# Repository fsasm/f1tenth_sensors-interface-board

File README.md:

# f1tenth_sensors-interface-board
Extension board for F1tenth cars with sensors and interfaces for humans (LEDs, display, buttons, etc.)

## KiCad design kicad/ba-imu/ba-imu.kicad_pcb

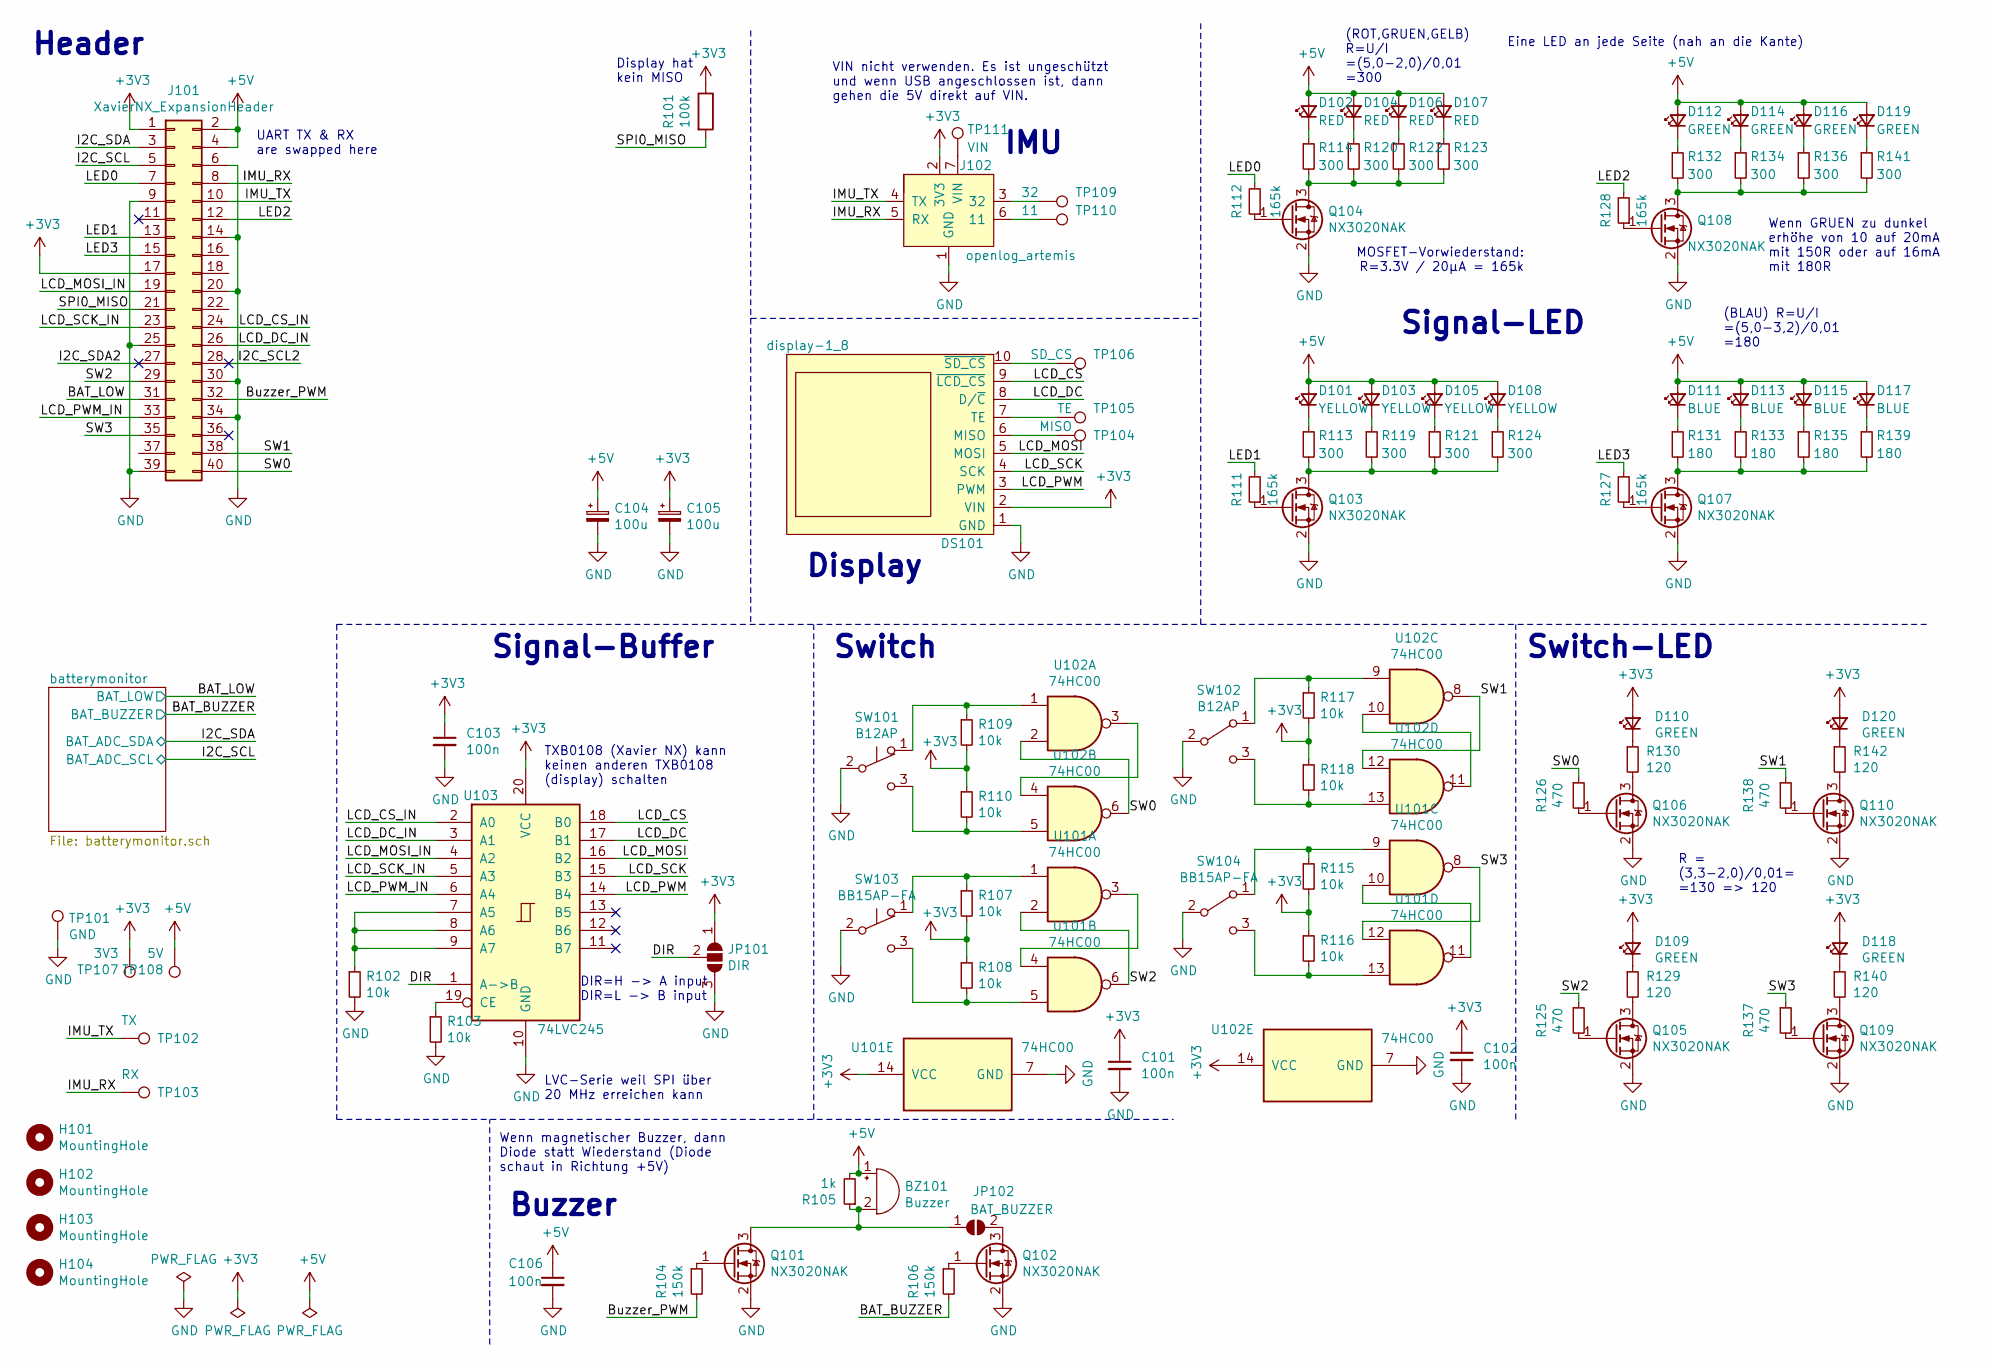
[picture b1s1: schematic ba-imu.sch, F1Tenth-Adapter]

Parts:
BZ101: Buzzer; Buzzer_TDK_PS1240P02BT_D12.2mm_H6.5mm; MPN PS1240P02BT; Digi-Key PN 445-2525-1-ND
C101, C102, C103, C106: 100n; C_1206_3216Metric
C104, C105: 100u; CP_Elec_6.3x7.7
D101, D103, D105, D108: YELLOW; LED_1206_3216Metric; MPN 156120YS75000; Digi-Key PN 732-5034-1-ND
D102, D104, D106, D107: RED; LED_1206_3216Metric; MPN 156120RS75000; Digi-Key PN 732-5030-1-ND
D109, D110, D112, D114, D116, D118, D119, D120: GREEN; LED_1206_3216Metric; MPN HSMQ-C150; Digi-Key PN 516-1444-1-ND
D111, D113, D115, D117: BLUE; LED_1206_3216Metric; MPN 156125BS75000; Digi-Key PN 732-13392-1-ND
DS101: display-1_8; display_SIP-10
H101, H102, H103, H104: MountingHole; MountingHole_2.5mm
J101: XavierNX_ExpansionHeader; PinHeader_2x20_P2.54mm_Vertical
J102: openlog_artemis; imu_SIP-7
JP101: DIR; SolderJumper-3_P1.3mm_Open_RoundedPad1.0x1.5mm
JP102: BAT_BUZZER; SolderJumper-2_P1.3mm_Open_RoundedPad1.0x1.5mm
Q101, Q102, Q103, Q104, Q105, Q106, Q107, Q108, Q109, Q110: NX3020NAK; SOT-23; MPN NX3020NAK; Digi-Key PN 1727-1285-1-ND
R101: 100k; R_1206_3216Metric
R102, R103, R107, R108, R109, R110, R115, R116, R117, R118: 10k; R_1206_3216Metric
R104, R106: 150k; R_1206_3216Metric
R105: 1k; R_1206_3216Metric
R111, R112, R127, R128: 165k; R_1206_3216Metric
R113, R114, R119, R120, R121, R122, R123, R124, R132, R134, R136, R141: 300; R_1206_3216Metric
R125, R126, R137, R138: 470; R_1206_3216Metric
R129, R130, R140, R142: 120; R_1206_3216Metric
R131, R133, R135, R139: 180; R_1206_3216Metric
SW101: B12AP; SW_Nidec_CFP2-1FC-AW; MPN B12AP; Digi-Key PN 360-1012-ND
SW102: B12AP; SW_Nidec_CF-LD-1DC-AR2W; MPN B12AP; Digi-Key PN 360-1012-ND
SW103: BB15AP-FA; SW_Nidec_CFP2-1FC-AW; MPN BB15AP-FA; Digi-Key PN 360-3753-ND
SW104: BB15AP-FA; SW_Nidec_CF-LD-1DC-AR2W; MPN BB15AP-FA; Digi-Key PN 360-3753-ND
TP101: GND; TestPoint_Pad_1.5x1.5mm
TP102: TX; TestPoint_Pad_D1.5mm
TP103: RX; TestPoint_Pad_D1.5mm
TP104: MISO; TestPoint_Pad_D1.5mm
TP105: TE; TestPoint_Pad_D1.5mm
TP106: SD_CS; TestPoint_Pad_D1.5mm
TP107: 3V3; TestPoint_Pad_D1.5mm
TP108: 5V; TestPoint_Pad_D1.5mm
TP109: 32; TestPoint_Pad_D1.5mm
TP110: 11; TestPoint_Pad_D1.5mm
TP111: VIN; TestPoint_Pad_D1.5mm
U101, U102: 74HC00; SOIC-14_3.9x8.7mm_P1.27mm; MPN SN74HC00DE4; Digi-Key PN 296-52930-ND
U103: 74LVC245; SOIC-20W_7.5x12.8mm_P1.27mm; MPN SN74LVC245ADW; Digi-Key PN 296-1232-5-ND

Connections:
+3V3: C101.1, C102.1, C103.1, C105.1, D109.2 (A), D110.2 (A), D118.2 (A), D120.2 (A), DS101.2 (VIN), J101.1, J101.17, J102.2 (3V3), JP101.1 (A), R101.1, R107.2, R108.1, R109.2, R110.1, R115.2, R116.1, R117.2, R118.1, TP107.1, U101.14 (VCC), U102.14 (VCC), U103.20 (VCC); also elsewhere on the board
+5V: BZ101.1 (-), C104.1, C106.1, D101.2 (A), D102.2 (A), D103.2 (A), D104.2 (A), D105.2 (A), D106.2 (A), D107.2 (A), D108.2 (A), D111.2 (A), D112.2 (A), D113.2 (A), D114.2 (A), D115.2 (A), D116.2 (A), D117.2 (A), D119.2 (A), J101.2, J101.4, R105.2, TP108.1
/BAT_BUZZER: R106.2; also elsewhere on the board
/BAT_LOW: J101.31; also elsewhere on the board
/Buzzer_PWM: J101.32, R104.2
/DIR: JP101.2 (C), U103.1 (A->B)
/I2C_SCL: J101.5; also elsewhere on the board
/I2C_SCL2: J101.28
/I2C_SDA: J101.3; also elsewhere on the board
/I2C_SDA2: J101.27
/IMU_RX: J101.8, J102.5 (RX), TP103.1
/IMU_TX: J101.10, J102.4 (TX), TP102.1
/LCD_CS: DS101.9 (~LCD_CS), U103.18 (B0)
/LCD_CS_IN: J101.24, U103.2 (A0)
/LCD_DC: DS101.8 (D/~C), U103.17 (B1)
/LCD_DC_IN: J101.26, U103.3 (A1)
/LCD_MOSI: DS101.5 (MOSI), U103.16 (B2)
/LCD_MOSI_IN: J101.19, U103.4 (A2)
/LCD_PWM: DS101.3 (PWM), U103.14 (B4)
/LCD_PWM_IN: J101.33, U103.6 (A4)
/LCD_SCK: DS101.4 (SCK), U103.15 (B3)
/LCD_SCK_IN: J101.23, U103.5 (A3)
/LED0: J101.7, R112.2
/LED1: J101.13, R111.2
/LED2: J101.12, R128.2
/LED3: J101.15, R127.2
/SPI0_MISO: J101.21, R101.2
/SW0: J101.40, R126.1, U102.2, U102.6
/SW1: J101.38, R138.1, U102.8, U102.12
/SW2: J101.29, R125.1, U101.2, U101.6
/SW3: J101.35, R137.1, U101.8, U101.12
GND: C101.2, C102.2, C103.2, C104.2, C105.2, C106.2, DS101.1 (GND), J101.6, J101.9, J101.14, J101.20, J101.25, J101.30, J101.34, J101.39, J102.1 (GND), JP101.3 (B), Q101.2 (S), Q102.2 (S), Q103.2 (S), Q104.2 (S), Q105.2 (S), Q106.2 (S), Q107.2 (S), Q108.2 (S), Q109.2 (S), Q110.2 (S), R102.2, R103.2, SW101.2 (B), SW102.2 (B), SW103.2 (B), SW104.2 (B), TP101.1, U101.7 (GND), U102.7 (GND), U103.10 (GND); also elsewhere on the board
unnamed: BZ101.2 (+), JP102.1 (A), Q101.3 (D), R105.1
unnamed: D101.1 (K), R113.1
unnamed: D102.1 (K), R114.1
unnamed: D103.1 (K), R119.1
unnamed: D104.1 (K), R120.1
unnamed: D105.1 (K), R121.1
unnamed: D106.1 (K), R122.1
unnamed: D107.1 (K), R123.1
unnamed: D108.1 (K), R124.1
unnamed: D109.1 (K), R129.1
unnamed: D110.1 (K), R130.1
unnamed: D111.1 (K), R131.1
unnamed: D112.1 (K), R132.1
unnamed: D113.1 (K), R133.1
unnamed: D114.1 (K), R134.1
unnamed: D115.1 (K), R135.1
unnamed: D116.1 (K), R136.1
unnamed: D117.1 (K), R139.1
unnamed: D118.1 (K), R140.1
unnamed: D119.1 (K), R141.1
unnamed: D120.1 (K), R142.1
unnamed: DS101.6 (MISO), TP104.1
unnamed: DS101.7 (TE), TP105.1
unnamed: DS101.10 (~SD_CS), TP106.1
unnamed: J102.3 (32), TP109.1
unnamed: J102.6 (11), TP110.1
unnamed: J102.7 (VIN), TP111.1
unnamed: JP102.2 (B), Q102.3 (D)
unnamed: Q101.1 (G), R104.1
unnamed: Q102.1 (G), R106.1
unnamed: Q103.1 (G), R111.1
unnamed: Q103.3 (D), R113.2, R119.2, R121.2, R124.2
unnamed: Q104.1 (G), R112.1
unnamed: Q104.3 (D), R114.2, R120.2, R122.2, R123.2
unnamed: Q105.1 (G), R125.2
unnamed: Q105.3 (D), R129.2
unnamed: Q106.1 (G), R126.2
unnamed: Q106.3 (D), R130.2
unnamed: Q107.1 (G), R127.1
unnamed: Q107.3 (D), R131.2, R133.2, R135.2, R139.2
unnamed: Q108.1 (G), R128.1
unnamed: Q108.3 (D), R132.2, R134.2, R136.2, R141.2
unnamed: Q109.1 (G), R137.2
unnamed: Q109.3 (D), R140.2
unnamed: Q110.1 (G), R138.2
unnamed: Q110.3 (D), R142.2
unnamed: R102.1, U103.7 (A5), U103.8 (A6), U103.9 (A7)
unnamed: R103.1, U103.19 (CE)
unnamed: R107.1, SW103.1 (A), U101.1
unnamed: R108.2, SW103.3 (C), U101.5
unnamed: R109.1, SW101.1 (A), U102.1
unnamed: R110.2, SW101.3 (C), U102.5
unnamed: R115.1, SW104.1 (A), U101.9
unnamed: R116.2, SW104.3 (C), U101.13
unnamed: R117.1, SW102.1 (A), U102.9
unnamed: R118.2, SW102.3 (C), U102.13
unnamed: U101.3, U101.4
unnamed: U101.10, U101.11
unnamed: U102.3, U102.4
unnamed: U102.10, U102.11

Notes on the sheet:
(ROT,GRUEN,GELB) R=U/I =(5,0-2,0)/0,01 =300
Wenn magnetischer Buzzer, dann Diode statt Wiederstand (Diode schaut in Richtung +5V)
VIN nicht verwenden. Es ist ungeschützt und wenn USB angeschlossen ist, dann gehen die 5V direkt auf VIN.
Eine LED an jede Seite (nah an die Kante)
DIR=H -> A input DIR=L -> B input
TXB0108 (Xavier NX) kann keinen anderen TXB0108 (display) schalten
(BLAU) R=U/I =(5,0-3,2)/0,01 =180
UART TX & RX are swapped here
Switch-LED
Switch
Buzzer
Signal-LED
LVC-Serie weil SPI über 20 MHz erreichen kann
Signal-Buffer
IMU
Display
Header
Display hat kein MISO
R = (3,3-2,0)/0,01= =130 => 120
Wenn GRUEN zu dunkel erhöhe von 10 auf 20mA mit 150R oder auf 16mA mit 180R
MOSFET-Vorwiederstand: R=3.3V / 20µA = 165k

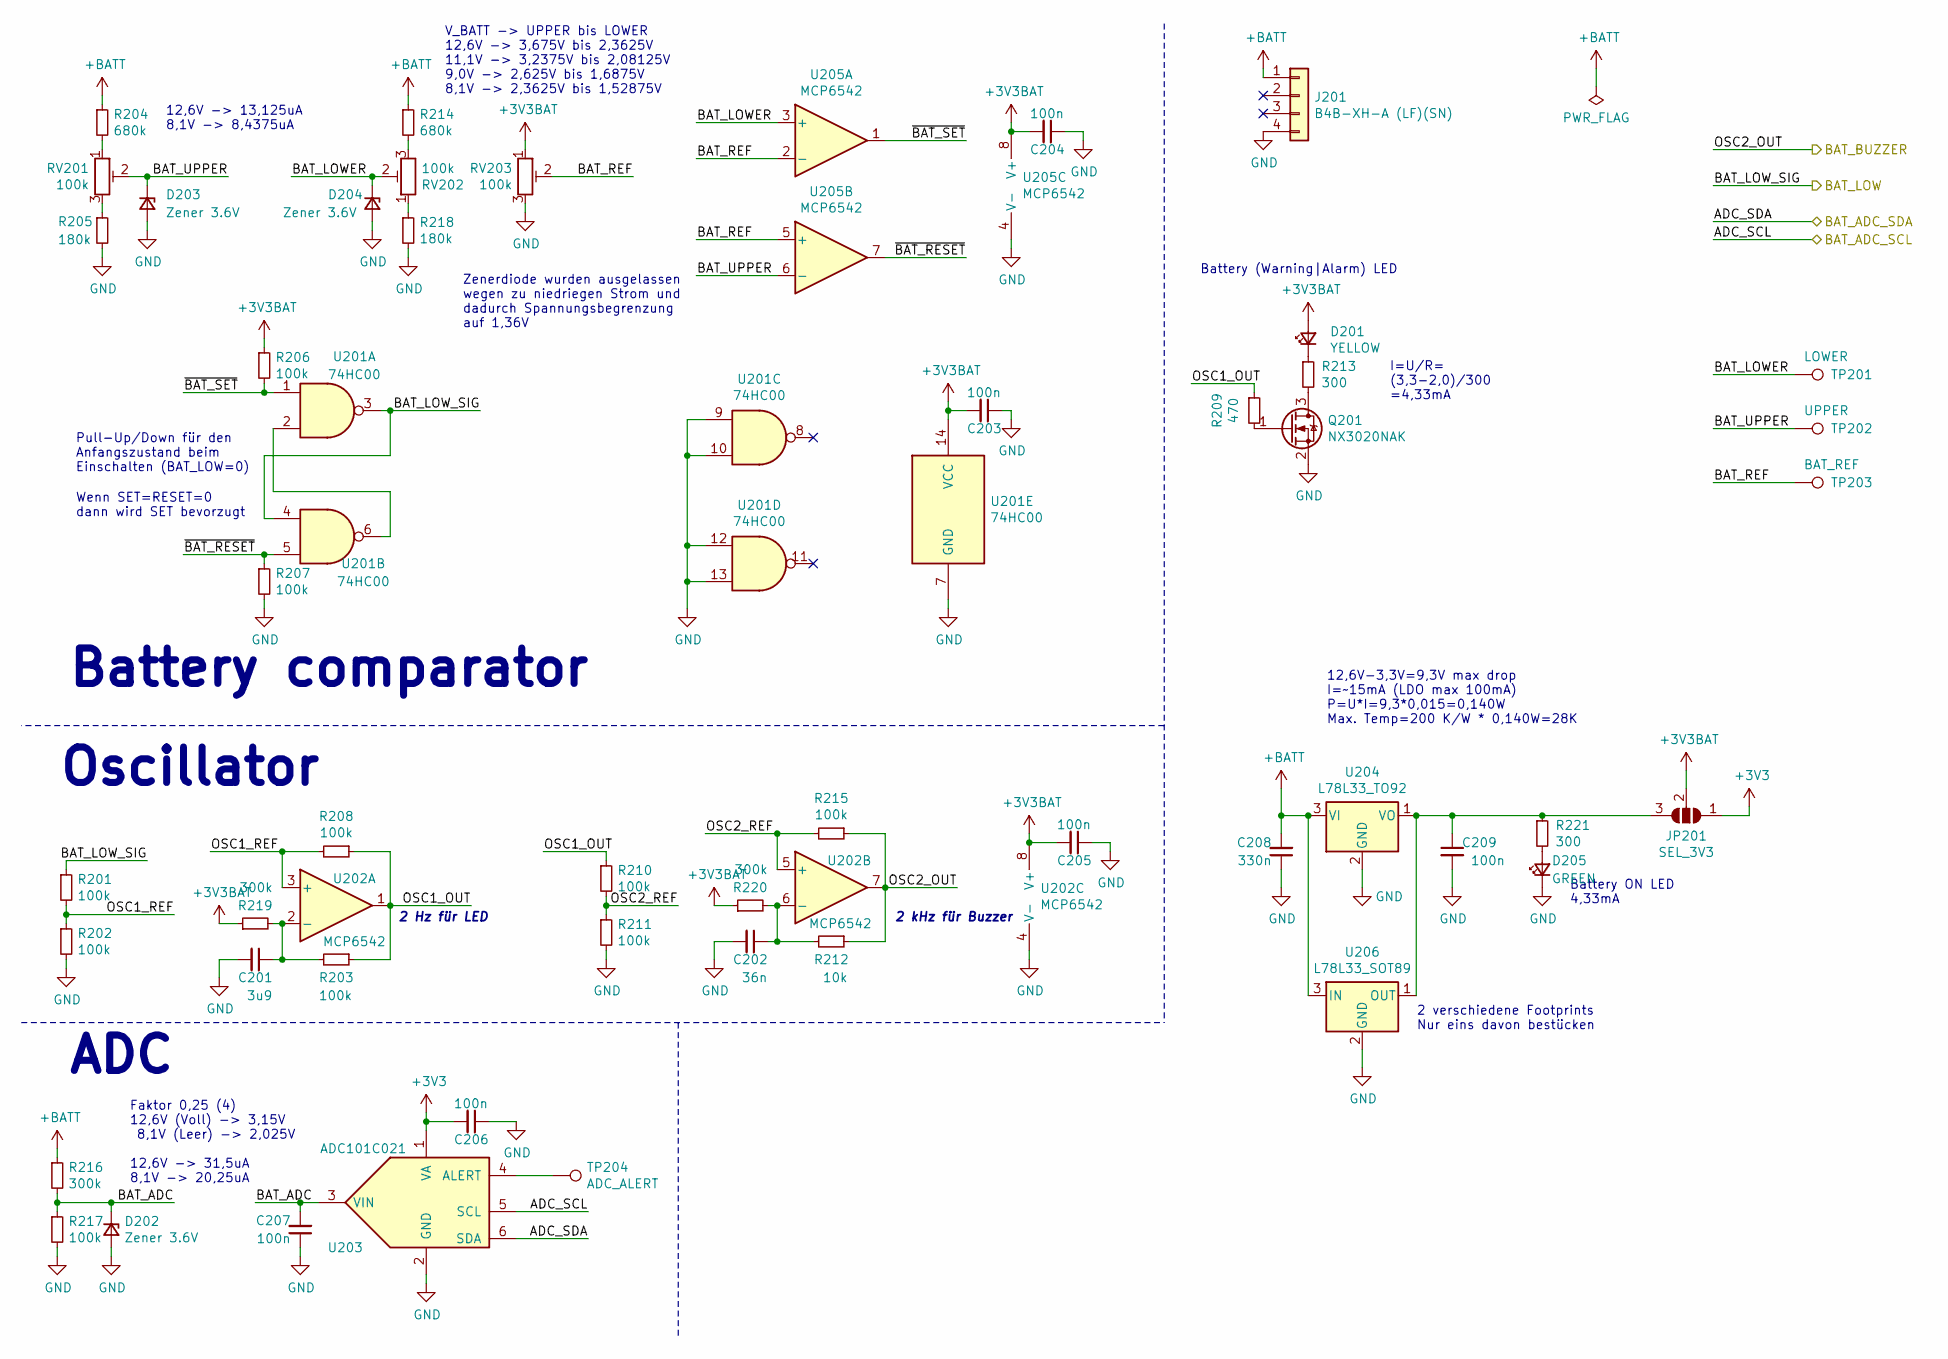
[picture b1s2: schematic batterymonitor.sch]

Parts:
C201: 3u9; C_1206_3216Metric
C202: 36n; C_1206_3216Metric
C203, C204, C205, C206, C207, C209: 100n; C_1206_3216Metric
C208: 330n; C_1206_3216Metric
D201: YELLOW; LED_1206_3216Metric; MPN 156120YS75000; Digi-Key PN 732-5034-1-ND
D202, D203, D204: Zener 3.6V; D_SOD-123; MPN MMSZ5227B-TP; Mouser PN 833-MMSZ5227B-TP
D205: GREEN; LED_1206_3216Metric; MPN 156120YS75000; Digi-Key PN 732-5034-1-ND
J201: B4B-XH-A (LF)(SN); JST_XH_B4B-XH-A_1x04_P2.50mm_Vertical; MPN B4B-XH-A(LF)(SN); Digi-Key PN 455-2249-ND
JP201: SEL_3V3; SolderJumper-3_P1.3mm_Open_RoundedPad1.0x1.5mm
Q201: NX3020NAK; SOT-23; MPN NX3020NAK; Digi-Key PN 1727-1285-1-ND
R201, R202, R203, R206, R207, R208, R210, R211, R215, R217: 100k; R_1206_3216Metric
R204, R214: 680k; R_1206_3216Metric
R205, R218: 180k; R_1206_3216Metric
R209: 470; R_1206_3216Metric
R212: 10k; R_1206_3216Metric
R213, R221: 300; R_1206_3216Metric
R216, R219, R220: 300k; R_1206_3216Metric
RV201, RV202, RV203: 100k; Potentiometer_Vishay_TS53YL_Vertical; MPN TS53YL204MR10; Digi-Key PN TS53YL-200KCT-ND
TP201: LOWER; TestPoint_Pad_D1.5mm
TP202: UPPER; TestPoint_Pad_D1.5mm
TP203: BAT_REF; TestPoint_Pad_D1.5mm
TP204: ADC_ALERT; TestPoint_Pad_D1.5mm
U201: 74HC00; SOIC-14_3.9x8.7mm_P1.27mm; MPN SN74HC00DE4; Digi-Key PN 296-52930-ND
U202, U205: MCP6542; SOIC-8_3.9x4.9mm_P1.27mm; MPN MCP6542-I/SN; Digi-Key PN MCP6542-I/SN-ND
U203: ADC101C021; SOT-23-6
U204: L78L33_TO92; TO-92_Inline
U206: L78L33_SOT89; SOT-89-3

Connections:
+3V3: C206.2, JP201.1 (A), U203.1 (VA); also elsewhere on the board
+3V3BAT: C203.2, C204.2, C205.2, D201.2 (A), JP201.2 (C), R206.1, R219.1, R220.1, RV203.1, U201.14 (VCC), U202.8 (V+), U205.8 (V+)
+BATT: C208.2, J201.1, R204.1, R214.1, R216.1, U204.3 (VI), U206.3 (IN)
/BAT_BUZZER: R212.1, R215.1, U202.7; also elsewhere on the board
/BAT_LOW: R201.1, U201.3, U201.4; also elsewhere on the board
/I2C_SCL: U203.5 (SCL); also elsewhere on the board
/I2C_SDA: U203.6 (SDA); also elsewhere on the board
/batterymonitor/BAT_ADC: C207.2, D202.1 (K), R216.2, R217.1, U203.3 (VIN)
/batterymonitor/BAT_LOWER: D204.1 (K), RV202.2, TP201.1, U205.3 (+)
/batterymonitor/BAT_REF: RV203.2, TP203.1, U205.2 (-), U205.5 (+)
/batterymonitor/BAT_UPPER: D203.1 (K), RV201.2, TP202.1, U205.6 (-)
/batterymonitor/OSC1_OUT: R203.1, R208.1, R209.1, R210.1, U202.1
/batterymonitor/OSC1_REF: R201.2, R202.1, R208.2, U202.3 (+)
/batterymonitor/OSC2_REF: R210.2, R211.1, R215.2, U202.5 (+)
/batterymonitor/~BAT_RESET: R207.1, U201.5, U205.7
/batterymonitor/~BAT_SET: R206.2, U201.1, U205.1
GND: C201.2, C202.2, C203.1, C204.1, C205.1, C206.1, C207.1, C208.1, C209.2, D202.2 (A), D203.2 (A), D204.2 (A), D205.1 (K), J201.4, Q201.2 (S), R202.2, R205.2, R207.2, R211.2, R217.2, R218.2, RV203.3, U201.7 (GND), U201.9, U201.10, U201.12, U201.13, U202.4 (V-), U203.2 (GND), U204.2 (GND), U205.4 (V-), U206.2 (GND); also elsewhere on the board
unnamed: C201.1, R203.2, R219.2, U202.2 (-)
unnamed: C202.1, R212.2, R220.2, U202.6 (-)
unnamed: C209.1, JP201.3 (B), R221.1, U204.1 (VO), U206.1 (OUT)
unnamed: D201.1 (K), R213.1
unnamed: D205.2 (A), R221.2
unnamed: Q201.1 (G), R209.2
unnamed: Q201.3 (D), R213.2
unnamed: R204.2, RV201.1
unnamed: R205.1, RV201.3
unnamed: R214.2, RV202.3
unnamed: R218.1, RV202.1
unnamed: TP204.1, U203.4 (ALERT)
unnamed: U201.2, U201.6

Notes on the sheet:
Pull-Up/Down für den Anfangszustand beim Einschalten (BAT_LOW=0)
Battery comparator
Oscillator
Wenn SET=RESET=0 dann wird SET bevorzugt
2 kHz für Buzzer
Battery (Warning|Alarm) LED
ADC
Faktor 0,25 (4) 12,6V (Voll) -> 3,15V 8,1V (Leer) -> 2,025V 12,6V -> 31,5uA 8,1V -> 20,25uA
V_BATT -> UPPER bis LOWER 12,6V -> 3,675V bis 2,3625V 11,1V -> 3,2375V bis 2,08125V 9,0V -> 2,625V bis 1,6875V 8,1V -> 2,3625V bis 1,52875V
2 Hz für LED
12,6V -> 13,125uA 8,1V -> 8,4375uA
Zenerdiode wurden ausgelassen wegen zu niedriegen Strom und dadurch Spannungsbegrenzung auf 1,36V
Battery ON LED 4,33mA
I=U/R= (3,3-2,0)/300 =4,33mA
2 verschiedene Footprints Nur eins davon bestücken
12,6V-3,3V=9,3V max drop I=~~15mA (LDO max 100mA) P=U*I=9,3*0,015=0,140W Max. Temp=200 K/W * 0,140W=28K

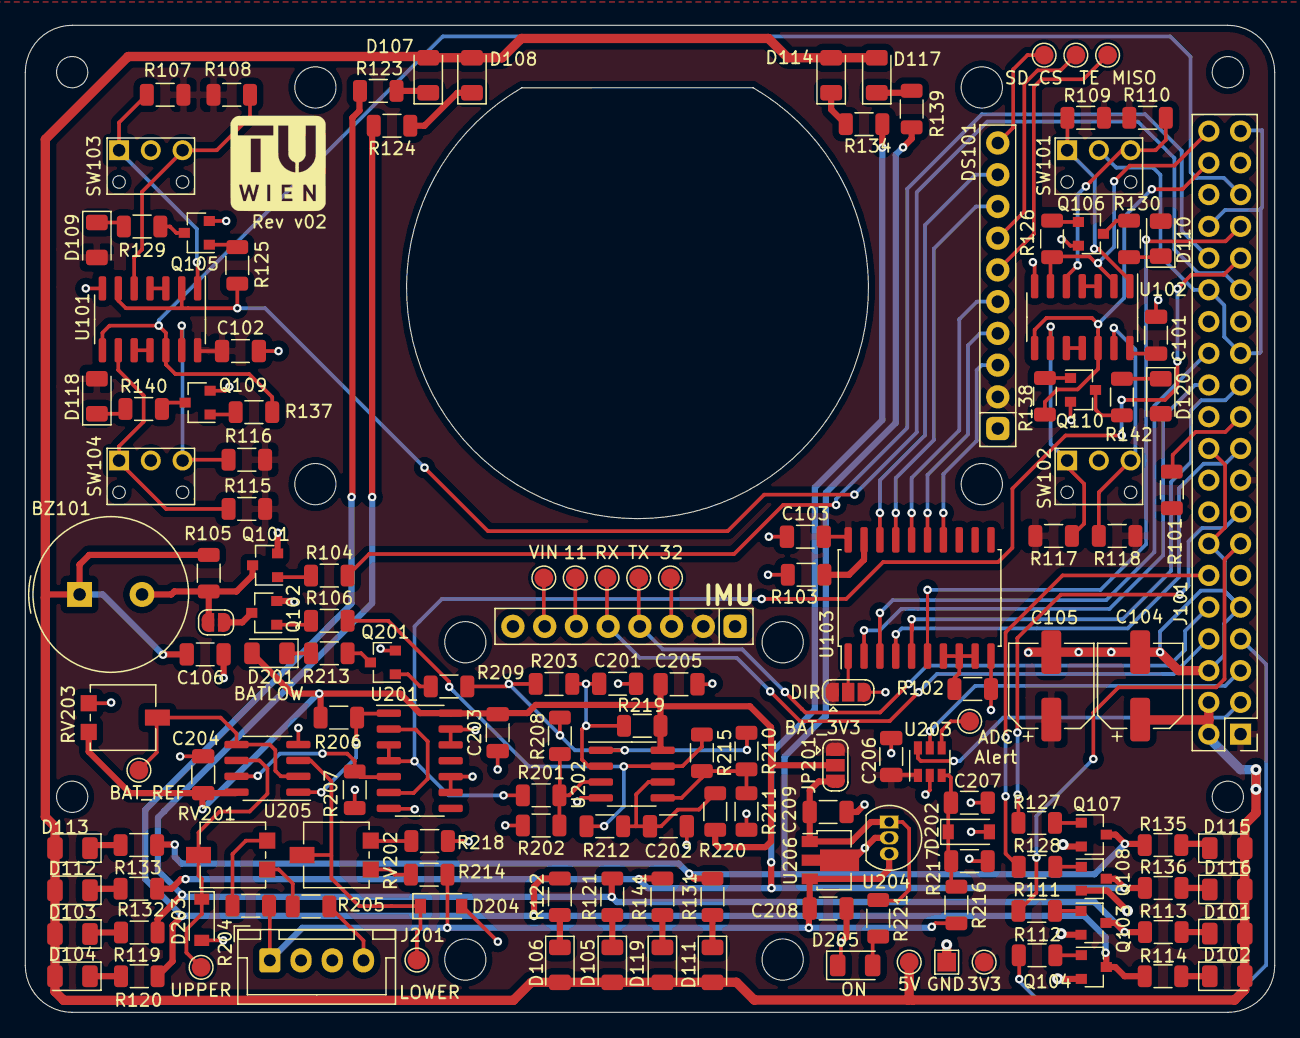
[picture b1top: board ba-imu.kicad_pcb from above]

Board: 2 copper layers, 100.0 x 79.0 mm, 157 parts (0 on the bottom side), 114 nets.

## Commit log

2022-10-09 add bachelor thesis
2022-10-10 add kicad project with final gerber files and interactive bom
